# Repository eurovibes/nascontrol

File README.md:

<!-- SPDX-FileCopyrightText: 2023 Benedikt Spranger <b.spranger@linutronix.de> -->
<!-- SPDX-License-Identifier: CERN-OHL-S-2.0 -->

# NAScontrol - A NAS control board

## License rules

nascontrol is provided under the terms of the CERN-OHL-S license
version 2 as provided in the LICENSES/CERN-OHL-S-2.0 file.

Instead of adding license boilerplates to the individual files,
nascontrol uses SPDX license identifiers, which are machine parseable
and considered legaly equivalent.

The SPDX license identifier in nascontrol shall be added at the first
possible line in a file which can contain a comment. This is normally the
first line except for scripts. Scripts require the #!PATH_TO_INTERPRETER tag
in the first line; place the SPDX identifier into the second line.

The SPDX license identifier is added in form of a comment.

## Copyright and License

> Copyright Benedikt Spranger 2023.
> This source describes Open Hardware and is licensed under the CERNOHL-S v2.
> You may redistribute and modify this source and make products using it
> under the terms of the CERN-OHL-S v2 (https://ohwr.org/cern ohl s v2.txt ).
> This source is distributed WITHOUT ANY EXPRESS OR IMPLIED WARRANTY, INCLUDING
> OF MERCHANTABILITY, SATISFACTORY QUALITY AND FITNESS FOR A PARTICULAR PURPOSE.
> Please see the CERN-OHL-S v2 for applicable conditions.
> Source location: https://github.com/eurovibes/nascontrol
> As per CERN-OHL-S v2 section 4, should You produce hardware based
> on this source, You must where practicable maintain the Source Location
> visible on the external case of the nascontrol or other products you
> make using this source.

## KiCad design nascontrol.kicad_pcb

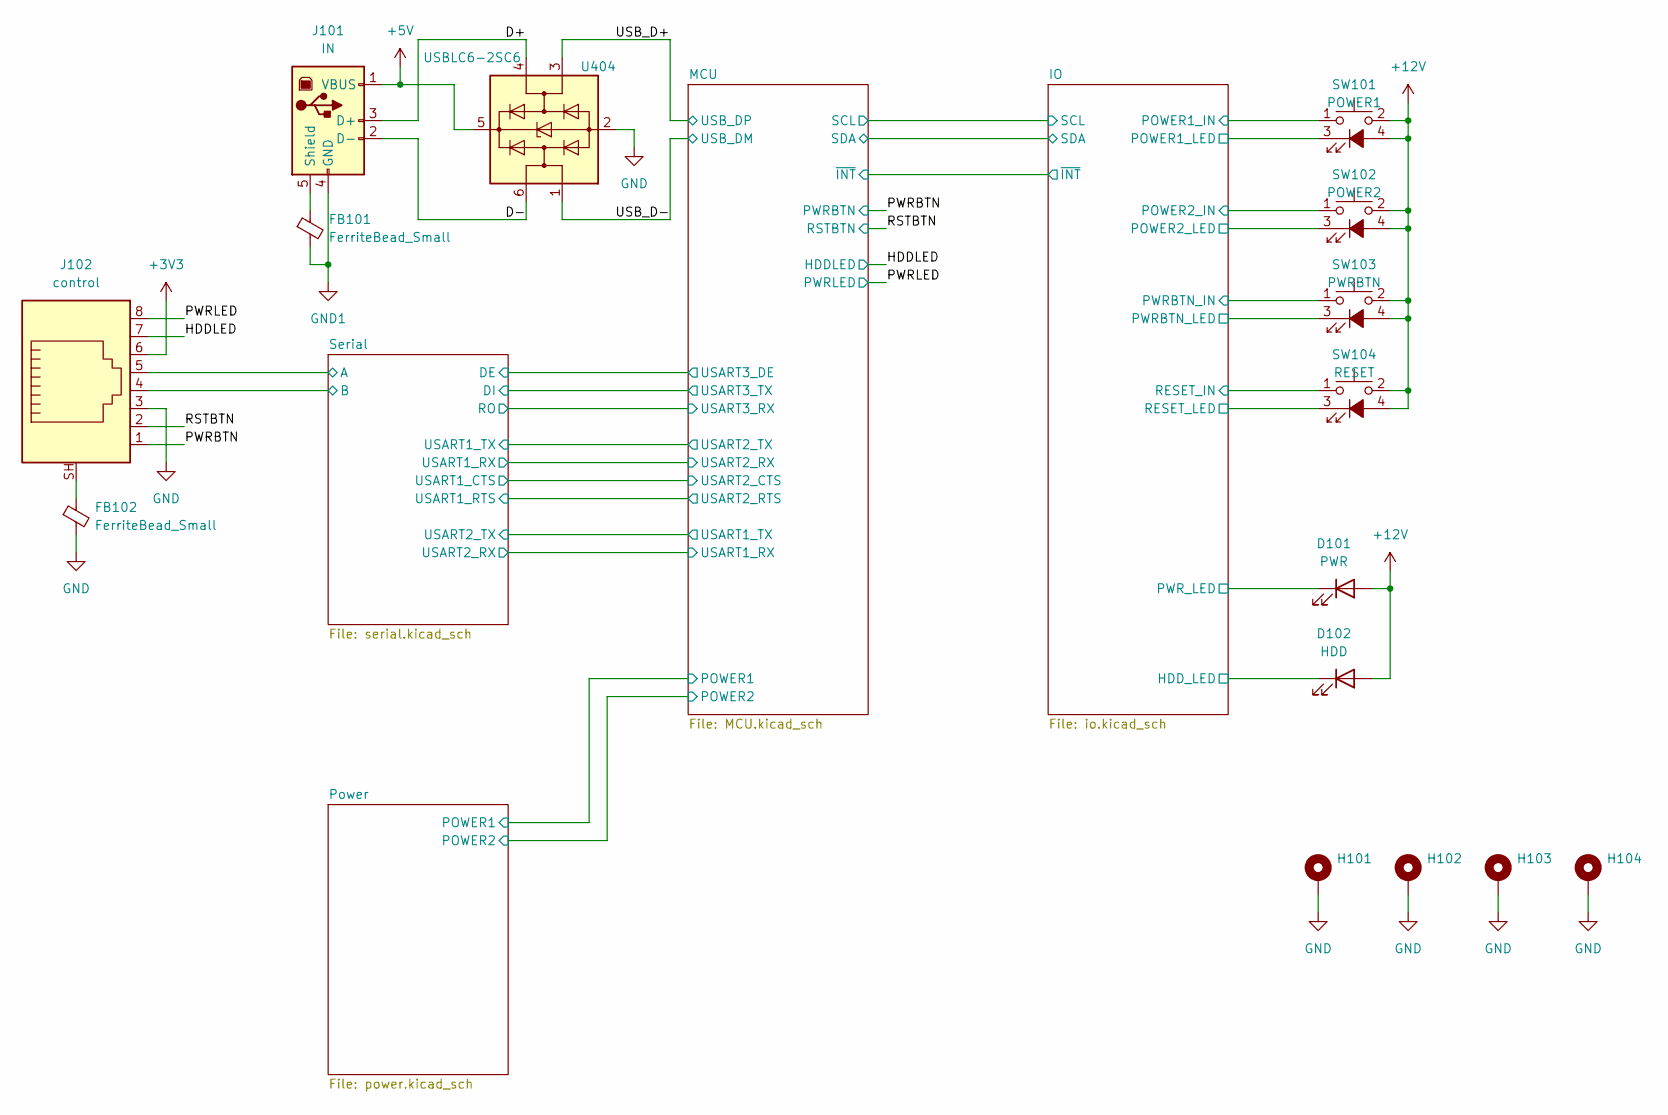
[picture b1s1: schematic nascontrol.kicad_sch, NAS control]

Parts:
D101: PWR; SolderWire-0.75sqmm_1x02_P4.8mm_D1.25mm_OD2.3mm; mpn N/A
D102: HDD; SolderWire-0.75sqmm_1x02_P4.8mm_D1.25mm_OD2.3mm; mpn N/A
FB101, FB102: FerriteBead_Small; L_0805_2012Metric; mpn GZ2012D101TF; LCSC# C1015
H101, H102, H103, H104: MountingHole_3.2mm_M3_Pad; mpn N/A
J101: IN; USB_B_Lumberg_2411_02_Horizontal; mpn TUEB4F2D0B
J102: control; MTJ-88GX1-FSD-PG6; mpn 6339160-1; LCSC# C125076
SW101: POWER1; SolderWire-0.75sqmm_1x04_P4.8mm_D1.25mm_OD2.3mm; mpn N/A
SW102: POWER2; SolderWire-0.75sqmm_1x04_P4.8mm_D1.25mm_OD2.3mm; mpn N/A
SW103: PWRBTN; SolderWire-0.75sqmm_1x04_P4.8mm_D1.25mm_OD2.3mm; mpn N/A
SW104: RESET; SolderWire-0.75sqmm_1x04_P4.8mm_D1.25mm_OD2.3mm; mpn N/A
U404: USBLC6-2SC6; SOT-23-6; mpn USBLC6-2SC6; LCSC# C2827654

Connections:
+12V: D101.2 (A), D102.2 (A), SW101.2, SW101.4 (A), SW102.2, SW102.4 (A), SW103.2, SW103.4 (A), SW104.2, SW104.4 (A); also elsewhere on the board
/HDDLED: J102.7; also elsewhere on the board
/IO/HDD_LED: D102.1 (K); also elsewhere on the board
/IO/POWER1_IN: SW101.1; also elsewhere on the board
/IO/POWER1_LED: SW101.3 (K); also elsewhere on the board
/IO/POWER2_IN: SW102.1; also elsewhere on the board
/IO/POWER2_LED: SW102.3 (K); also elsewhere on the board
/IO/PWRBTN_IN: SW103.1; also elsewhere on the board
/IO/PWRBTN_LED: SW103.3 (K); also elsewhere on the board
/IO/PWR_LED: D101.1 (K); also elsewhere on the board
/IO/RESET_IN: SW104.1; also elsewhere on the board
/IO/RESET_LED: SW104.3 (K); also elsewhere on the board
/PWRBTN: J102.1; also elsewhere on the board
/PWRLED: J102.8; also elsewhere on the board
/RSTBTN: J102.2; also elsewhere on the board
/Serial/A: J102.5; also elsewhere on the board
/Serial/B: J102.4; also elsewhere on the board
GND: FB102.2, H101.1, H102.1, H103.1, H104.1, J102.3, U404.2 (GND); also elsewhere on the board
GND1: FB101.2, J101.4 (GND); also elsewhere on the board
unnamed: FB101.1, J101.5 (Shield)
unnamed: FB102.1, J102.SH

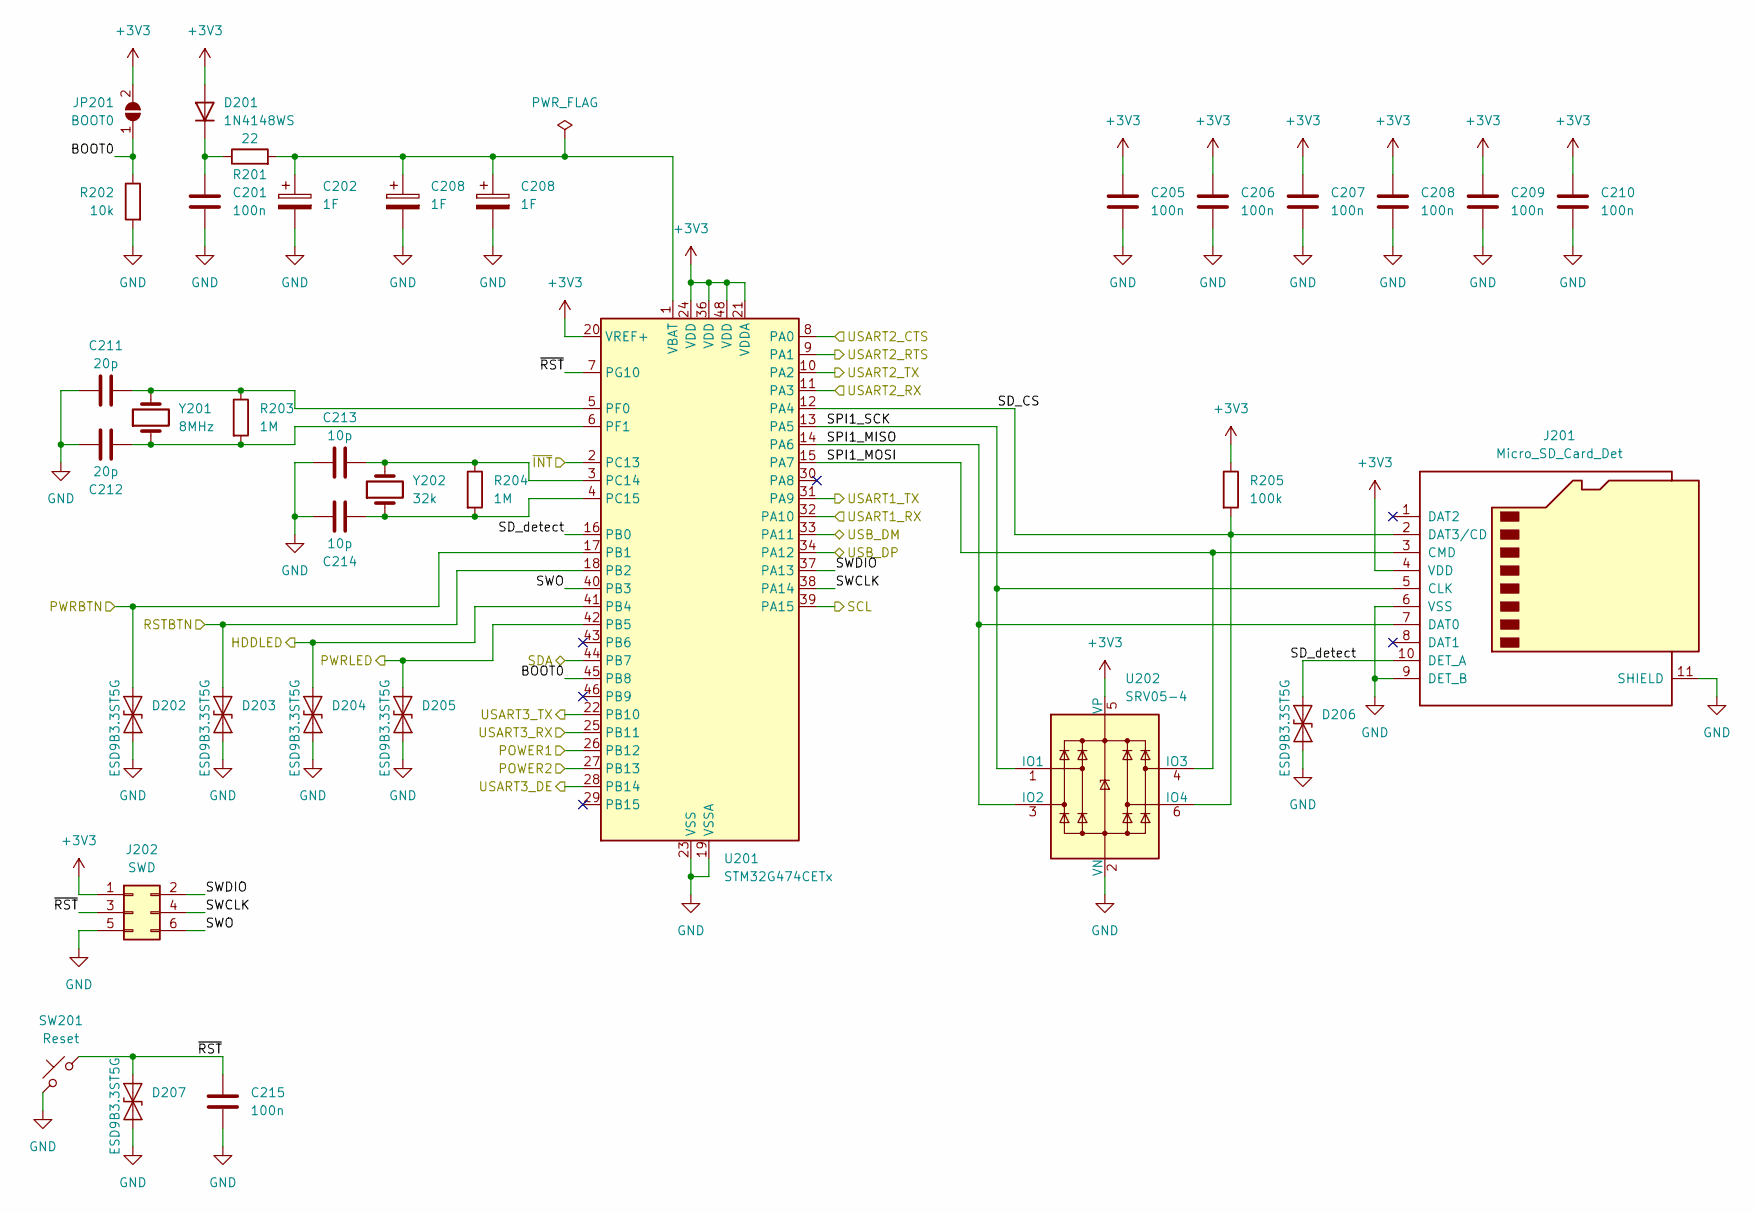
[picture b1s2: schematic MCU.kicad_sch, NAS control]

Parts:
C201, C205, C206, C207, C209, C210, C215: 100n; C_0402_1005Metric; mpn CL05B104KB54PNC; LCSC# C307331
C202, C208: 1F; CP_Radial_D8.0mm_P3.50mm; mpn SCV0001C0-003R0LTZ
C211, C212: 20p; C_0402_1005Metric; mpn 0402CG200J500NT; LCSC# C1554
C213, C214: 10p; C_0402_1005Metric; mpn CL05C100JB5NNNC; LCSC# C32949
D201: 1N4148WS; D_SOD-323; mpn 1N4148WS; LCSC# C2128
D202, D203, D204, D205, D206, D207: ESD9B3.3ST5G; D_SOD-923; mpn ESD9B3.3ST5G; LCSC# C96512
J201: Micro_SD_Card_Det; microSD_HC_Molex_104031-0811; mpn 1040310811; LCSC# C585350
J202: SWD; Tag-Connect_TC2030-IDC-FP_2x03_P1.27mm_Vertical; mpn TC2030
JP201: BOOT0; SolderJumper-2_P1.3mm_Open_Pad1.0x1.5mm; mpn N/A
R201: 22; R_1206_3216Metric; mpn 1206W4F220JT5E; LCSC# C17958
R202: 10k; R_0402_1005Metric; mpn 0402WGF1002TCE; LCSC# C25744
R203, R204: 1M; R_0402_1005Metric; mpn 0402WGF1004TCE; LCSC# C26083
R205: 100k; R_0402_1005Metric; mpn 0402WGF1003TCE; LCSC# C25741
SW201: Reset; SW_Tactile_SPST_Angled_PTS645Vx58-2LFS; mpn PTS645VL58-2 LFS
U201: STM32G474CETx; LQFP-48_7x7mm_P0.5mm; mpn STM32G474CET6; LCSC# C730125
U202: SRV05-4; SOT-23-6; mpn SRV05-4; LCSC# C558418
Y201: 8MHz; Crystal_SMD_5032-2Pin_5.0x3.2mm; mpn X50328MSB2GI; LCSC# C115962
Y202: 32k; Crystal_SMD_3215-2Pin_3.2x1.5mm; mpn Q13FC1350000400; LCSC# C32346

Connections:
/HDDLED: D204.2 (A2), U201.41 (PB4); also elsewhere on the board
/IO/SCL: U201.39 (PA15); also elsewhere on the board
/IO/SDA: U201.44 (PB7); also elsewhere on the board
/IO/~INT: U201.2 (PC13); also elsewhere on the board
/MCU/BOOT0: JP201.1 (A), R202.1, U201.45 (PB8)
/MCU/POWER1: U201.26 (PB12); also elsewhere on the board
/MCU/POWER2: U201.27 (PB13); also elsewhere on the board
/MCU/SD_CS: J201.2 (DAT3/CD), R205.2, U201.12 (PA4), U202.6 (IO4)
/MCU/SD_detect: D206.2 (A2), J201.10 (DET_A), U201.16 (PB0)
/MCU/SPI1_MISO: J201.7 (DAT0), U201.14 (PA6), U202.3 (IO2)
/MCU/SPI1_MOSI: J201.3 (CMD), U201.15 (PA7), U202.4 (IO3)
/MCU/SPI1_SCK: J201.5 (CLK), U201.13 (PA5), U202.1 (IO1)
/MCU/SWCLK: J202.4, U201.38 (PA14)
/MCU/SWDIO: J202.2, U201.37 (PA13)
/MCU/SWO: J202.6, U201.40 (PB3)
/MCU/USART1_RX: U201.32 (PA10); also elsewhere on the board
/MCU/USART1_TX: U201.31 (PA9); also elsewhere on the board
/MCU/USART2_CTS: U201.8 (PA0); also elsewhere on the board
/MCU/USART2_RTS: U201.9 (PA1); also elsewhere on the board
/MCU/USART2_RX: U201.11 (PA3); also elsewhere on the board
/MCU/USART2_TX: U201.10 (PA2); also elsewhere on the board
/MCU/USART3_DE: U201.28 (PB14); also elsewhere on the board
/MCU/USART3_RX: U201.25 (PB11); also elsewhere on the board
/MCU/USART3_TX: U201.22 (PB10); also elsewhere on the board
/MCU/~RST: C215.1, D207.2 (A2), J202.3, SW201.1, U201.7 (PG10)
/PWRBTN: D202.2 (A2), U201.17 (PB1); also elsewhere on the board
/PWRLED: D205.2 (A2), U201.42 (PB5); also elsewhere on the board
/RSTBTN: D203.2 (A2), U201.18 (PB2); also elsewhere on the board
GND: C201.2, C202.2, C205.2, C206.2, C207.2, C208.2, C209.2, C210.2, C211.1, C212.1, C213.1, C214.1, C215.2, D202.1 (A1), D203.1 (A1), D204.1 (A1), D205.1 (A1), D206.1 (A1), D207.1 (A1), J201.6 (VSS), J201.9 (DET_B), J201.11 (SHIELD), J202.5, R202.2, SW201.2, U201.19 (VSSA), U201.23 (VSS), U201.35 (VSS), U201.47 (VSS), U202.2 (VN); also elsewhere on the board
unnamed: C201.1, D201.1 (K), R201.1
unnamed: C211.2, R203.1, U201.5 (PF0), Y201.2
unnamed: C212.2, R203.2, U201.6 (PF1), Y201.1
unnamed: C213.2, R204.1, U201.3 (PC14), Y202.2
unnamed: C214.2, R204.2, U201.4 (PC15), Y202.1

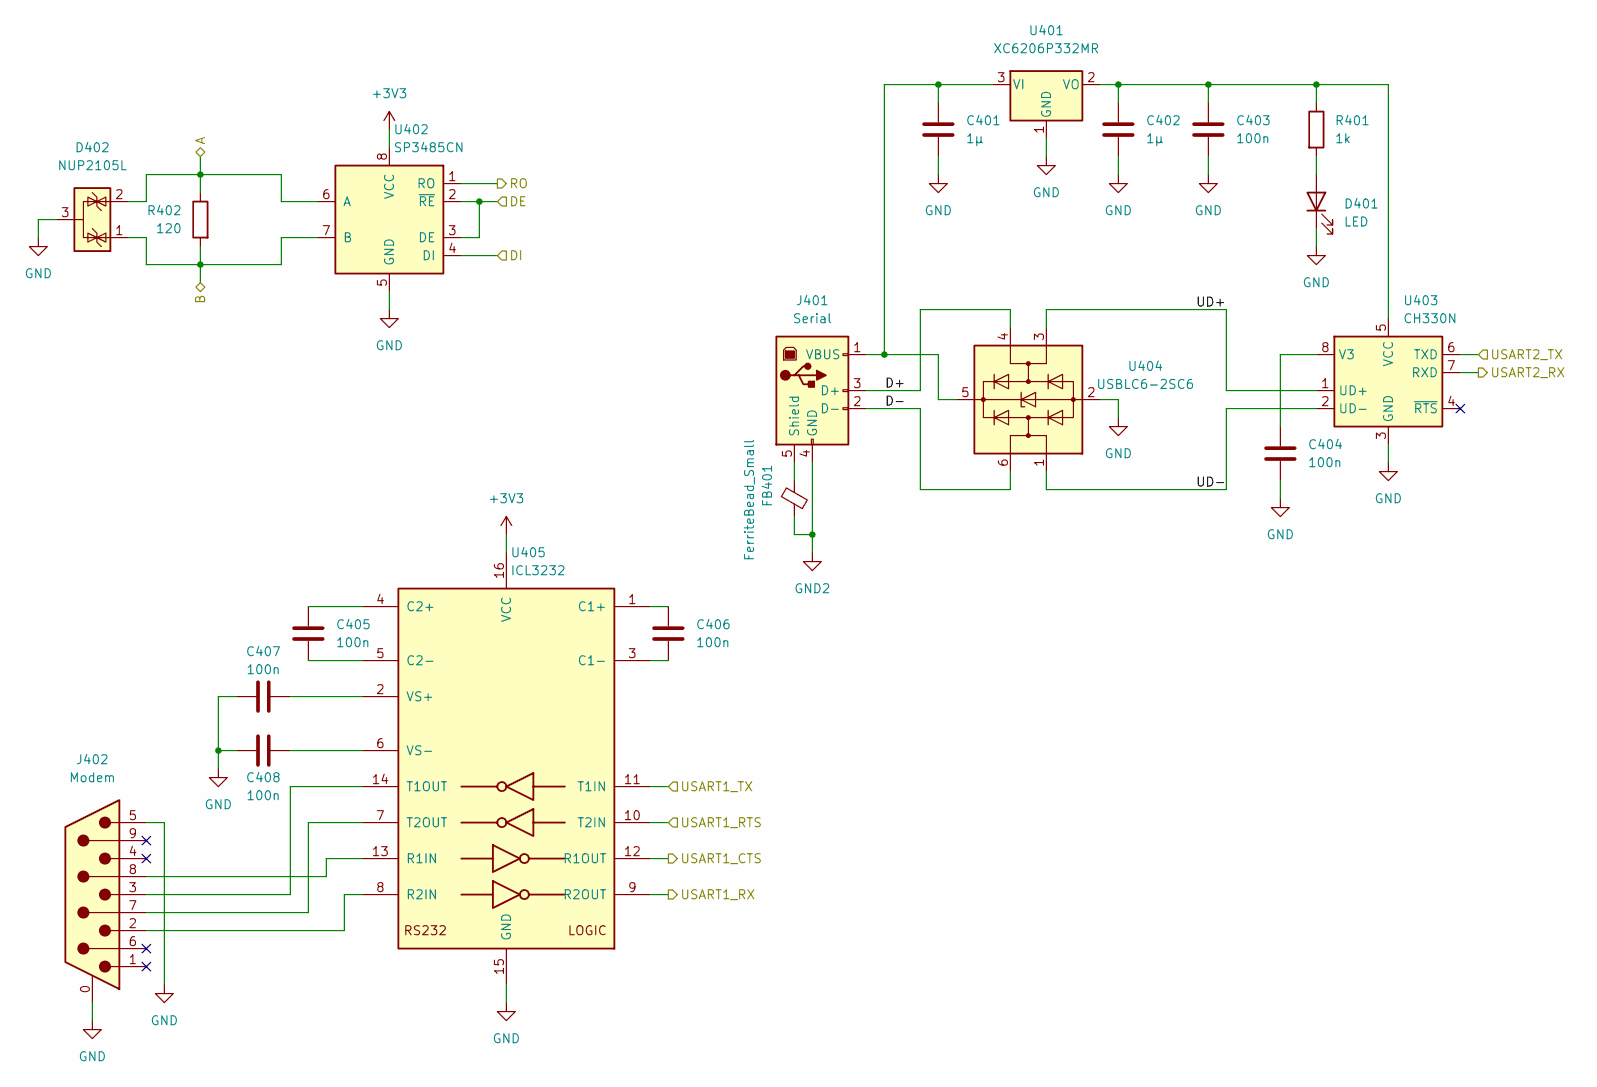
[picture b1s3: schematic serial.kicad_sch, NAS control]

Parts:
C401, C402: 1µ; C_0805_2012Metric; mpn CL21B105KBFNNNE; LCSC# C28323
C403, C404, C405, C406, C407, C408: 100n; C_0402_1005Metric; mpn CL05B104KB54PNC; LCSC# C307331
D401: LED; LED_0603_1608Metric; mpn 19-217/GHC-YR1S2/3T; LCSC# C72043
D402: NUP2105L; SOT-23; mpn NUP2105LT1G; LCSC# C2890118
FB401: FerriteBead_Small; L_0805_2012Metric; mpn GZ2012D101TF; LCSC# C1015
J401: Serial; USB_B_Lumberg_2411_02_Horizontal; mpn TUEB4F2D0B
J402: Modem; DSUB-9_Male_Horizontal_P2.77x2.84mm_EdgePinOffset7.70mm_Hou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; mpn DE09-PL-24
R401: 1k; R_0402_1005Metric; mpn 0402WGF1001TCE; LCSC# C11702
R402: 120; R_1206_3216Metric; mpn 1206W4F1200T5E; LCSC# C17909
U401: XC6206P332MR; SOT-23; mpn XC6206P332MR; LCSC# C5446
U402: SP3485CN; SOIC-8_3.9x4.9mm_P1.27mm; mpn SP3485EN-L/TR; LCSC# C8963
U403: CH330N; SOIC-8_3.9x4.9mm_P1.27mm; mpn CH340N; LCSC# C506813
U404: USBLC6-2SC6; SOT-23-6; mpn USBLC6-2SC6; LCSC# C2827654
U405: ICL3232; TSSOP-16_4.4x5mm_P0.65mm; mpn SP3232EEY-L/TR; LCSC# C13482

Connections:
/MCU/USART1_RX: U403.7 (RXD); also elsewhere on the board
/MCU/USART1_TX: U403.6 (TXD); also elsewhere on the board
/MCU/USART2_CTS: U405.12 (R1OUT); also elsewhere on the board
/MCU/USART2_RTS: U405.10 (T2IN); also elsewhere on the board
/MCU/USART2_RX: U405.9 (R2OUT); also elsewhere on the board
/MCU/USART2_TX: U405.11 (T1IN); also elsewhere on the board
/MCU/USART3_DE: U402.2 (~RE), U402.3 (DE); also elsewhere on the board
/MCU/USART3_RX: U402.1 (RO); also elsewhere on the board
/MCU/USART3_TX: U402.4 (DI); also elsewhere on the board
/Serial/A: D402.2 (K), R402.1, U402.6 (A); also elsewhere on the board
/Serial/B: D402.1 (K), R402.2, U402.7 (B); also elsewhere on the board
GND: C401.2, C402.2, C403.2, C404.2, C407.1, C408.1, D401.1 (K), D402.3 (A), J402.0 (PAD), J402.5, U401.1 (GND), U402.5 (GND), U403.3 (GND), U404.2 (GND), U405.15 (GND); also elsewhere on the board
GND2: FB401.2, J401.4 (GND); also elsewhere on the board
unnamed: C402.1, C403.1, R401.1, U401.2 (VO), U403.5 (VCC)
unnamed: C404.1, U403.8 (V3)
unnamed: C405.1, U405.4 (C2+)
unnamed: C405.2, U405.5 (C2-)
unnamed: C406.1, U405.1 (C1+)
unnamed: C406.2, U405.3 (C1-)
unnamed: C407.2, U405.2 (VS+)
unnamed: C408.2, U405.6 (VS-)
unnamed: D401.2 (A), R401.2
unnamed: FB401.1, J401.5 (Shield)
unnamed: J402.2, U405.8 (R2IN)
unnamed: J402.3, U405.14 (T1OUT)
unnamed: J402.7, U405.7 (T2OUT)
unnamed: J402.8, U405.13 (R1IN)

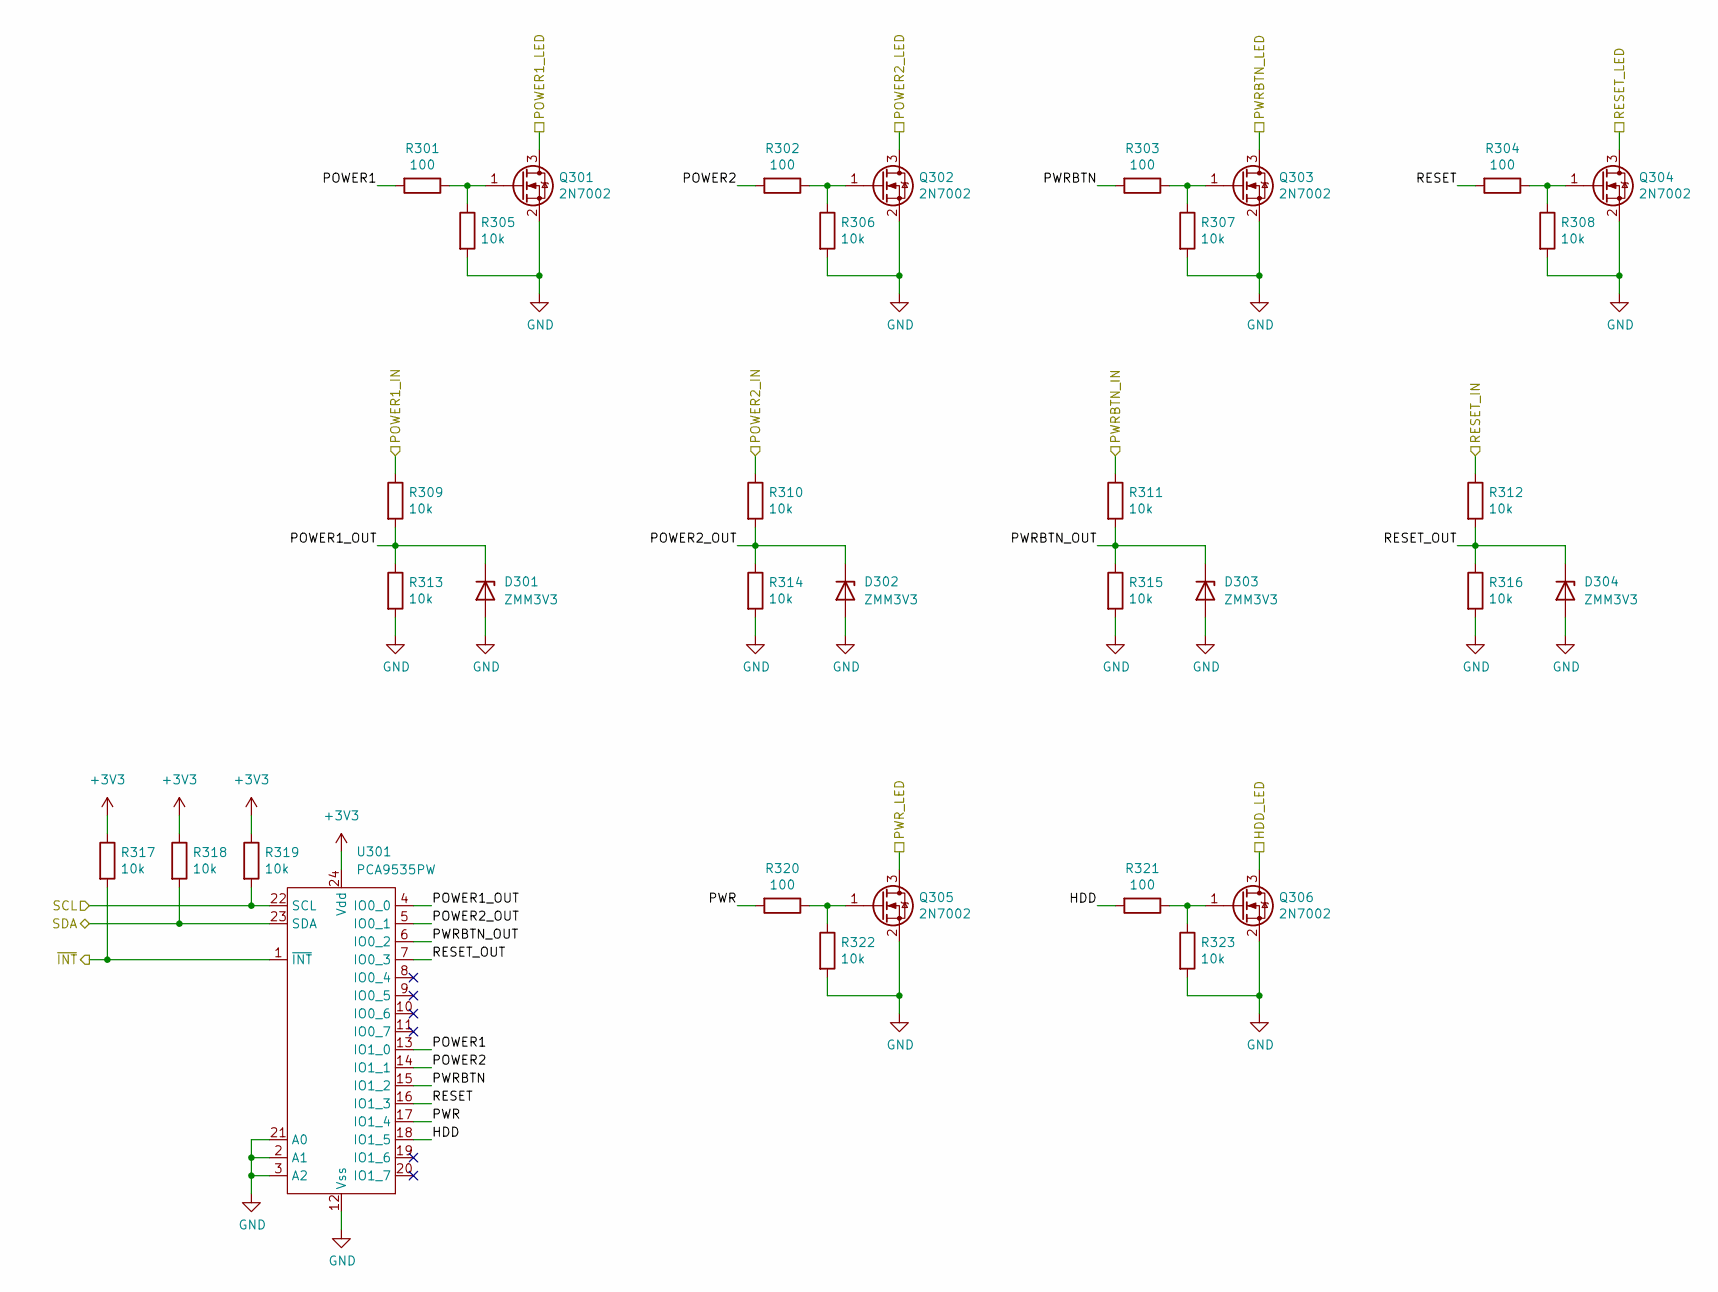
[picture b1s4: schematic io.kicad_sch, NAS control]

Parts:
D301, D302, D303, D304: ZMM3V3; D_MiniMELF; mpn ZMM3V3-M; LCSC# C8056
Q301, Q302, Q303, Q304, Q305, Q306: 2N7002; SOT-23; mpn 2N7002; LCSC# C8545
R301, R302, R303, R304, R320, R321: 100; R_0402_1005Metric; mpn 0402WGF1000TCE; LCSC# C25076
R305, R306, R307, R308, R309, R310, R311, R312, R313, R314, R315, R316, R317, R318, R319, R322, R323: 10k; R_0402_1005Metric; mpn 0402WGF1002TCE; LCSC# C25744
U301: PCA9535PW; TSSOP-24_4.4x7.8mm_P0.65mm; mpn PCA9535PW,118; LCSC# C255606

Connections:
/IO/HDD: R321.2, U301.18 (IO1_5)
/IO/HDD_LED: Q306.3 (D); also elsewhere on the board
/IO/POWER1: R301.2, U301.13 (IO1_0)
/IO/POWER1_IN: R309.1; also elsewhere on the board
/IO/POWER1_LED: Q301.3 (D); also elsewhere on the board
/IO/POWER1_OUT: D301.1 (K), R309.2, R313.1, U301.4 (IO0_0)
/IO/POWER2: R302.2, U301.14 (IO1_1)
/IO/POWER2_IN: R310.1; also elsewhere on the board
/IO/POWER2_LED: Q302.3 (D); also elsewhere on the board
/IO/POWER2_OUT: D302.1 (K), R310.2, R314.1, U301.5 (IO0_1)
/IO/PWR: R320.2, U301.17 (IO1_4)
/IO/PWRBTN: R303.2, U301.15 (IO1_2)
/IO/PWRBTN_IN: R311.1; also elsewhere on the board
/IO/PWRBTN_LED: Q303.3 (D); also elsewhere on the board
/IO/PWRBTN_OUT: D303.1 (K), R311.2, R315.1, U301.6 (IO0_2)
/IO/PWR_LED: Q305.3 (D); also elsewhere on the board
/IO/RESET: R304.2, U301.16 (IO1_3)
/IO/RESET_IN: R312.1; also elsewhere on the board
/IO/RESET_LED: Q304.3 (D); also elsewhere on the board
/IO/RESET_OUT: D304.1 (K), R312.2, R316.1, U301.7 (IO0_3)
/IO/SCL: R319.2, U301.22 (SCL); also elsewhere on the board
/IO/SDA: R318.2, U301.23 (SDA); also elsewhere on the board
/IO/~INT: R317.2, U301.1 (~INT); also elsewhere on the board
GND: D301.2 (A), D302.2 (A), D303.2 (A), D304.2 (A), Q301.2 (S), Q302.2 (S), Q303.2 (S), Q304.2 (S), Q305.2 (S), Q306.2 (S), R305.2, R306.2, R307.2, R308.2, R313.2, R314.2, R315.2, R316.2, R322.2, R323.2, U301.2 (A1), U301.3 (A2), U301.12 (Vss), U301.21 (A0); also elsewhere on the board
unnamed: Q301.1 (G), R301.1, R305.1
unnamed: Q302.1 (G), R302.1, R306.1
unnamed: Q303.1 (G), R303.1, R307.1
unnamed: Q304.1 (G), R304.1, R308.1
unnamed: Q305.1 (G), R320.1, R322.1
unnamed: Q306.1 (G), R321.1, R323.1

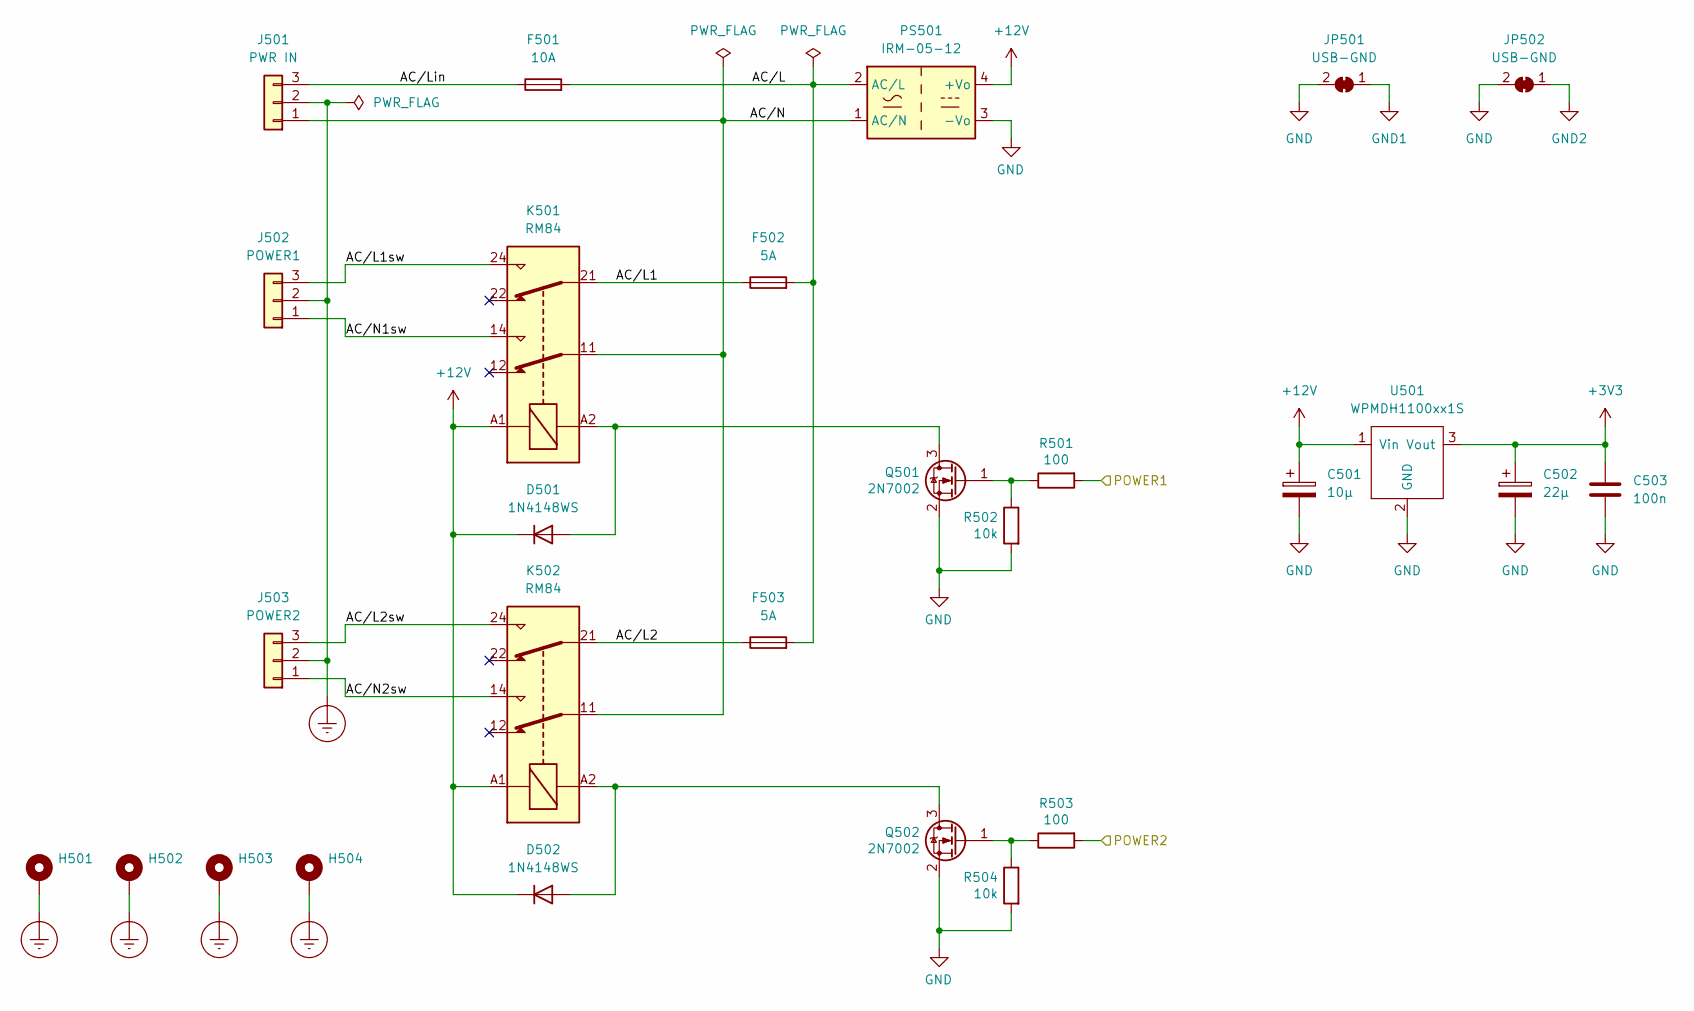
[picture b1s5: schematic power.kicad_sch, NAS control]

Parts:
C501: 10µ; CP_Elec_5x5.4; mpn RVT1H100M0505; LCSC# C72487
C502: 22µ; CP_Elec_6.3x5.4; mpn RVT1H220M0605; LCSC# C72505
C503: 100n; C_0402_1005Metric; mpn CL05B104KB54PNC; LCSC# C307331
D501, D502: 1N4148WS; D_SOD-323; mpn 1N4148WS; LCSC# C2128
F501: 10A; SolderWire-1.5sqmm_1x02_P6mm_D1.7mm_OD3mm_Relief; mpn R3-12E
F502, F503: 5A; SolderWire-1.5sqmm_1x02_P6mm_D1.7mm_OD3mm_Relief; mpn R3-12E
H501, H502, H503, H504: MountingHole_3.2mm_M3_Pad
J501: PWR IN; SolderWire-1.5sqmm_1x03_P6mm_D1.7mm_OD3mm_Relief; mpn N/A
J502: POWER1; SolderWire-1.5sqmm_1x03_P6mm_D1.7mm_OD3mm_Relief; mpn N/A
J503: POWER2; SolderWire-1.5sqmm_1x03_P6mm_D1.7mm_OD3mm_Relief; mpn N/A
JP501, JP502: USB-GND; SolderJumper-2_P1.3mm_Bridged2Bar_Pad1.0x1.5mm; mpn N/A
K501, K502: RM84; Relay_DPDT_Finder_40.52; mpn RM84-2012-35-1012
PS501: IRM-05-12; Converter_ACDC_MeanWell_IRM-05-xx_THT; mpn IRM-05-12
Q501, Q502: 2N7002; SOT-23; mpn 2N7002; LCSC# C8545
R501, R503: 100; R_0402_1005Metric; mpn 0402WGF1000TCE; LCSC# C25076
R502, R504: 10k; R_0402_1005Metric; mpn 0402WGF1002TCE; LCSC# C25744
U501: WPMDH1100xx1S; mpn AMSRB1-783.3JZ

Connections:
+12V: C501.1, D501.1 (K), D502.1 (K), K501.A1, K502.A1, PS501.4 (+Vo), U501.1 (Vin); also elsewhere on the board
/MCU/POWER1: R501.2; also elsewhere on the board
/MCU/POWER2: R503.2; also elsewhere on the board
/Power/AC/L: F501.2, F502.2, F503.2, PS501.2 (AC/L)
/Power/AC/L1: F502.1, K501.21
/Power/AC/L1sw: J502.3, K501.24
/Power/AC/L2: F503.1, K502.21
/Power/AC/L2sw: J503.3, K502.24
/Power/AC/Lin: F501.1, J501.3
/Power/AC/N: J501.1, K501.11, K502.11, PS501.1 (AC/N)
/Power/AC/N1sw: J502.1, K501.14
/Power/AC/N2sw: J503.1, K502.14
Earth_Protective: H501.1, H502.1, H503.1, H504.1, J501.2, J502.2, J503.2
GND: C501.2, C502.2, C503.2, JP501.2 (B), JP502.2 (B), PS501.3 (-Vo), Q501.2 (S), Q502.2 (S), R502.2, R504.2, U501.2 (GND); also elsewhere on the board
GND1: JP501.1 (A); also elsewhere on the board
GND2: JP502.1 (A); also elsewhere on the board
unnamed: D501.2 (A), K501.A2, Q501.3 (D)
unnamed: D502.2 (A), K502.A2, Q502.3 (D)
unnamed: Q501.1 (G), R501.1, R502.1
unnamed: Q502.1 (G), R503.1, R504.1

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
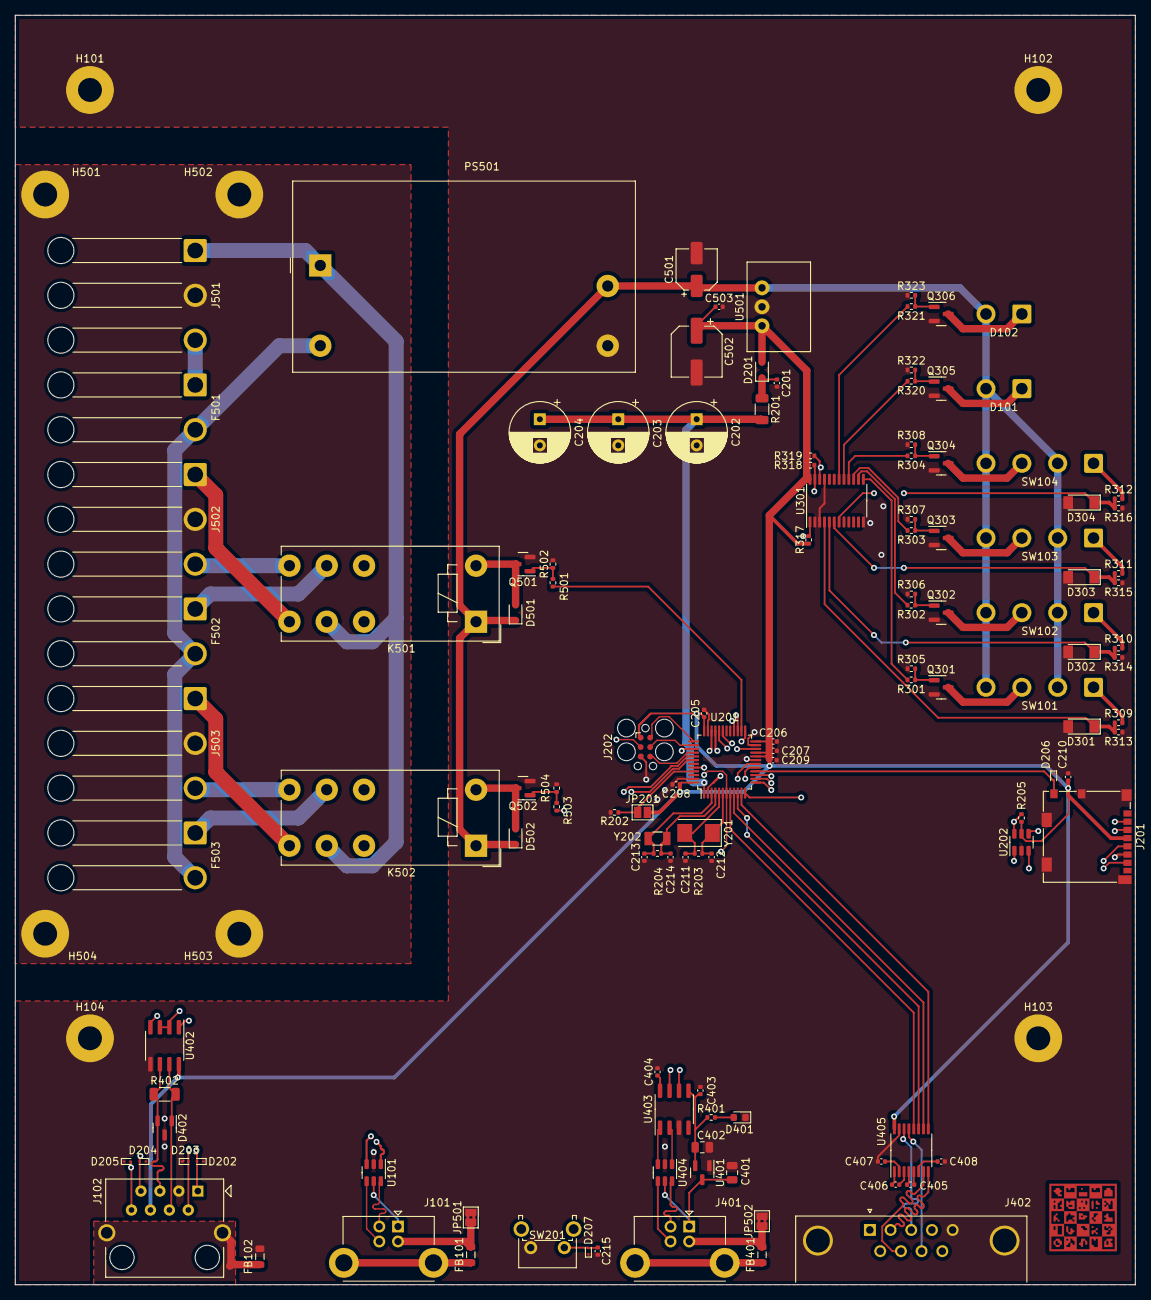
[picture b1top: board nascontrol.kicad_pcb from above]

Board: 4 copper layers, 150.0 x 170.0 mm, 131 parts (0 on the bottom side), 107 nets.

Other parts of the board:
C208#2: 100n; C_0402_1005Metric
C208#3: 1F; CP_Radial_D8.0mm_P3.50mm
U404#2: USBLC6-2SC6; SOT-23-6

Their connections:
GND: C208#2.2, C208#3.2, U404#2.2 (GND); also elsewhere on the board

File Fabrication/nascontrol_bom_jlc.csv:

"Comment","Designator","Footprint","LCSC Part #"
"10p","C213,C214","C_0402_1005Metric","C32949"
"20p","C211,C212","C_0402_1005Metric","C1554"
"100n","C201,C205,C206,C207,C208,C209,C210,C215,C403,C404,C405,C406,C407,C408,C503","C_0402_1005Metric","C307331"
"1µ","C401,C402","C_0805_2012Metric","C28323"
"10µ","C501","CP_Elec_5x5.4","C72487"
"22µ","C502","CP_Elec_6.3x5.4","C72505"
"1N4148WS","D201,D501,D502","D_SOD-323","C2128"
"ESD9B3.3ST5G","D202,D203,D204,D205,D206,D207","D_SOD-923","C96512"
"LED","D401","LED_0603_1608Metric","C72043"
"NUP2105L","D402","SOT-23","C2890118"
"ZMM3V3","D301,D302,D303,D304","D_MiniMELF","C8056"
"FerriteBead_Small","FB101,FB102,FB401","L_0805_2012Metric","C1015"
"Micro_SD_Card_Det","J201","microSD_HC_Molex_104031-0811","C585350"
"control","J102","MTJ-88GX1-FSD-PG6","C125076"
"2N7002","Q301,Q302,Q303,Q304,Q305,Q306,Q501,Q502","SOT-23","C8545"
"22","R201","R_1206_3216Metric","C17958"
"100","R301,R302,R303,R304,R320,R321,R501,R503","R_0402_1005Metric","C25076"
"120","R402","R_1206_3216Metric","C17909"
"1k","R401","R_0402_1005Metric","C11702"
"10k","R202,R305,R306,R307,R308,R309,R310,R311,R312,R313,R314,R315,R316,R317,R318,R319,R322,R323,R502,R504","R_0402_1005Metric","C25744"
"100k","R205","R_0402_1005Metric","C25741"
"1M","R203,R204","R_0402_1005Metric","C26083"
"CH330N","U403","SOIC-8_3.9x4.9mm_P1.27mm","C506813"
"ICL3232","U405","TSSOP-16_4.4x5mm_P0.65mm","C13482"
"PCA9535PW","U301","TSSOP-24_4.4x7.8mm_P0.65mm","C255606"
"SP3485CN","U402","SOIC-8_3.9x4.9mm_P1.27mm","C8963"
"SRV05-4","U202","SOT-23-6","C558418"
"STM32G474CETx","U201","LQFP-48_7x7mm_P0.5mm","C730125"
"USBLC6-2SC6","U101,U404","SOT-23-6","C2827654"
"XC6206P332MR","U401","SOT-23","C5446"
"32k","Y202","Crystal_SMD_3215-2Pin_3.2x1.5mm","C32346"
"8MHz","Y201","Crystal_SMD_5032-2Pin_5.0x3.2mm","C115962"

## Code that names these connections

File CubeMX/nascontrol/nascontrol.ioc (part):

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Mcu.Name=STM32G474C(B-C-E)Tx
Mcu.Package=LQFP48
Mcu.UserName=STM32G474CETx
PA0.Mode=CTS_RTS
PA0.Signal=USART2_CTS
PA1.Mode=CTS_RTS
PA1.Signal=USART2_RTS
PA10.Mode=Asynchronous
PA10.Signal=USART1_RX
PA11.Mode=Device
PA11.Signal=USB_DM
PA12.Mode=Device
PA12.Signal=USB_DP
PA13.Mode=Trace_Asynchronous_SW
PA13.Signal=SYS_JTMS-SWDIO
PA14.Mode=Trace_Asynchronous_SW
PA14.Signal=SYS_JTCK-SWCLK
PA2.Mode=Asynchronous
PA2.Signal=USART2_TX
PA3.Mode=Asynchronous
PA3.Signal=USART2_RX
PA4.GPIOParameters=GPIO_Label
PA4.GPIO_Label=SD_CS
PA4.Signal=GPIO_Output
PA5.Mode=Full_Duplex_Master
PA5.Signal=SPI1_SCK
PA6.Mode=Full_Duplex_Master
PA6.Signal=SPI1_MISO
PA7.Mode=Full_Duplex_Master
PA7.Signal=SPI1_MOSI
PA9.Mode=Asynchronous
PA9.Signal=USART1_TX
PB0.GPIOParameters=GPIO_Label
PB0.GPIO_Label=SD_detect
PB0.Signal=GPXTI0
PB1.GPIOParameters=GPIO_Label
PB1.GPIO_Label=PWRBTN
PB1.Signal=GPXTI1
PB10.Mode=Asynchronous
PB10.Signal=USART3_TX
PB11.Mode=Asynchronous
PB11.Signal=USART3_RX
PB12.GPIOParameters=GPIO_Label
PB12.GPIO_Label=POWER1
PB12.Signal=GPIO_Output
PB13.GPIOParameters=GPIO_Label
PB13.GPIO_Label=POWER2
PB13.Signal=GPIO_Output
PB14.Mode=Hardware Flow Control (RS485)
PB14.Signal=USART3_DE
PB2.GPIOParameters=GPIO_Label
PB2.GPIO_Label=RSTBTN
PB2.Signal=GPXTI2
PB3.Mode=Trace_Asynchronous_SW
PB3.Signal=SYS_JTDO-SWO
PB4.GPIOParameters=GPIO_Label
PB4.GPIO_Label=HDDLED
PB4.Signal=GPIO_Output
PB5.GPIOParameters=GPIO_Label
PB5.GPIO_Label=PWRLED
PB5.Signal=GPIO_Output
PB7.Mode=SMBus-two-wire-Interface
PB7.Signal=I2C1_SDA
PB8-BOOT0.Mode=SMBus-two-wire-Interface
PB8-BOOT0.Signal=I2C1_SCL
PC13.Mode=SYS_WakeUp1
PC13.Signal=SYS_WKUP2
PC14-OSC32_IN.Mode=LSE-External-Oscillator
PC14-OSC32_IN.Signal=RCC_OSC32_IN
PC15-OSC32_OUT.Mode=LSE-External-Oscillator
PC15-OSC32_OUT.Signal=RCC_OSC32_OUT
PF0-OSC_IN.Mode=HSE-External-Oscillator
PF0-OSC_IN.Signal=RCC_OSC_IN
PF1-OSC_OUT.Mode=HSE-External-Oscillator
PF1-OSC_OUT.Signal=RCC_OSC_OUT
RCC.HSE_VALUE=8000000
RCC.SYSCLKFreq_VALUE=16000000
board=custom

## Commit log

2023-01-21 Add high voltage protector enclosure
2023-01-21 Update node 12 actions
    Node 12 is EOL. Update Actions relaying on Node 12 to newer versions.
2023-01-21 Initial
2023-01-21 Add mesh regeneration script
2023-01-21 Add frontpanel
2023-01-21 Initial gh-pages commit
2023-01-21 Deploying to gh-pages from @ eurovibes/nascontrol@c96da2c09baea337de77e05d62a15608f8acf09d 🚀

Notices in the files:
MCU.kicad_sch:
This work is licensed under the CERN-OHL-S v2
